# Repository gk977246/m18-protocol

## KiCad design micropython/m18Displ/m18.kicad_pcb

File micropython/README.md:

# M18 Protocol Micropython

Since someone posted pictures of Esp32-devices with display - I wanted such a device as quicktester.

I have no experience with micropython, but with help from qwen, i made a version for micropython.

Important: set Tx_pin low on boot(dumb charge count increases). I have added a boot.py file

## Hardware

I made a test pcb with Esp32C3-mini, Oled or Spi-display, and uart connections for cyd

Includes Mp1584 (buck-module), level-shifter, and Spud-Isolator

## Dont use Cyd with buck converter(the dumb charge counter increases) -- power it with usb and use read-button

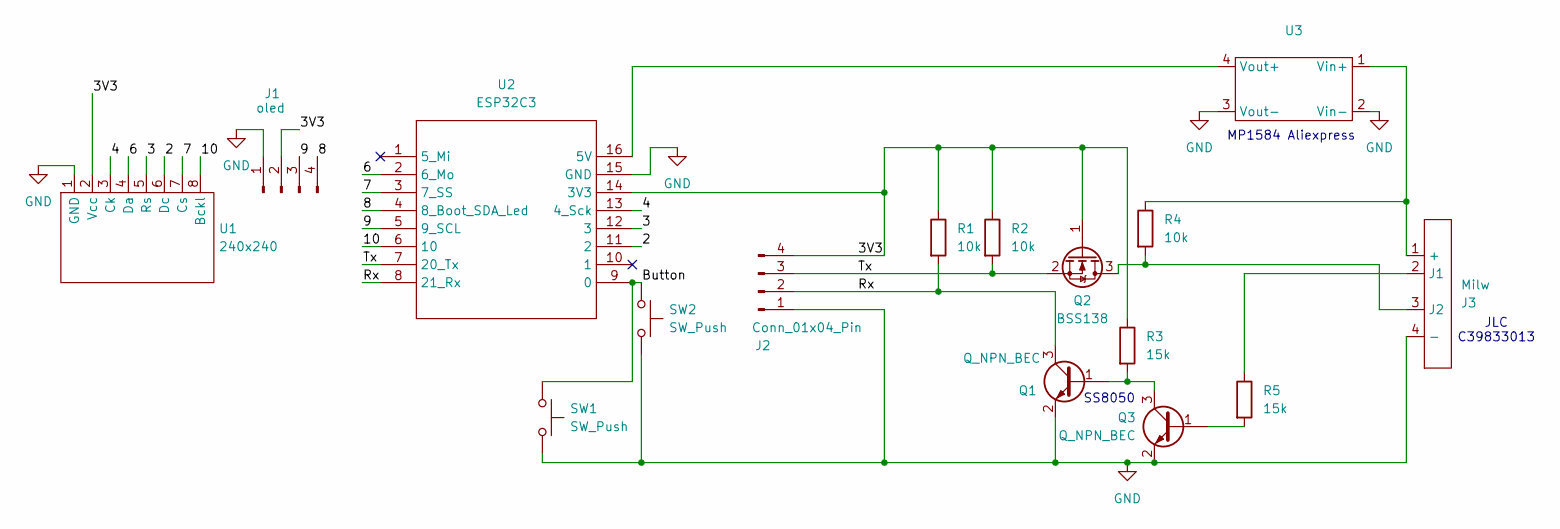
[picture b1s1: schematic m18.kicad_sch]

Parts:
J1: oled; 128x64Oled4Pin
J2: Conn_01x04_Pin; PinSocket_1x04_P2.54mm_Vertical
J3: Milw; Milw_Spade
Q1, Q3: Q_NPN_BEC; SOT-23
Q2: BSS138; SOT-23
R1, R2, R4: 10k; R_0603_1608Metric
R3, R5: 15k; R_0603_1608Metric
SW1: SW_Push; Sw_edge
SW2: SW_Push; SW_Push_1P1T_NO_6x6mm_H9.5mm
U1: 240x240; 170x320_7789
U2: ESP32C3; Esp32_C3_mini_module
U3: mp1584

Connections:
/2: U1.6 (Dc), U2.11 (2)
/3: U1.5 (Rs), U2.12 (3)
/3V3: J1.2, J2.4, Q2.1 (G), R1.1, R2.1, R3.1, U1.2 (Vcc), U2.14 (3V3)
/4: U1.3 (Ck), U2.13 (4_Sck)
/6: U1.4 (Da), U2.2 (6_Mo)
/7: U1.7 (Cs), U2.3 (7_SS)
/8: J1.4, U2.4 (8_Boot_SDA_Led)
/9: J1.3, U2.5 (9_SCL)
/10: U1.8 (Bckl), U2.6 (10)
/Button: SW1.1, SW2.1, U2.9 (0)
/Rx: J2.2, Q1.3 (C), R1.2, U2.8 (21_Rx)
/Tx: J2.3, Q2.2 (S), R2.2, U2.7 (20_Tx)
GND: J1.1, J2.1, J3.4 (-), Q1.2 (E), Q3.2 (E), SW1.2, SW2.2, U1.1 (GND), U2.15 (GND), U3.2 (Vin-), U3.3 (Vout-)
unnamed: J3.1 (+), R4.1, U3.1 (Vin+)
unnamed: J3.2 (J1), R5.1
unnamed: J3.3 (J2), Q2.3 (D), R4.2
unnamed: Q1.1 (B), Q3.3 (C), R3.2
unnamed: Q3.1 (B), R5.2
unnamed: U2.16 (5V), U3.4 (Vout+)

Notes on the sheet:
SS8050
MP1584 Aliexpress
JLC C39833013

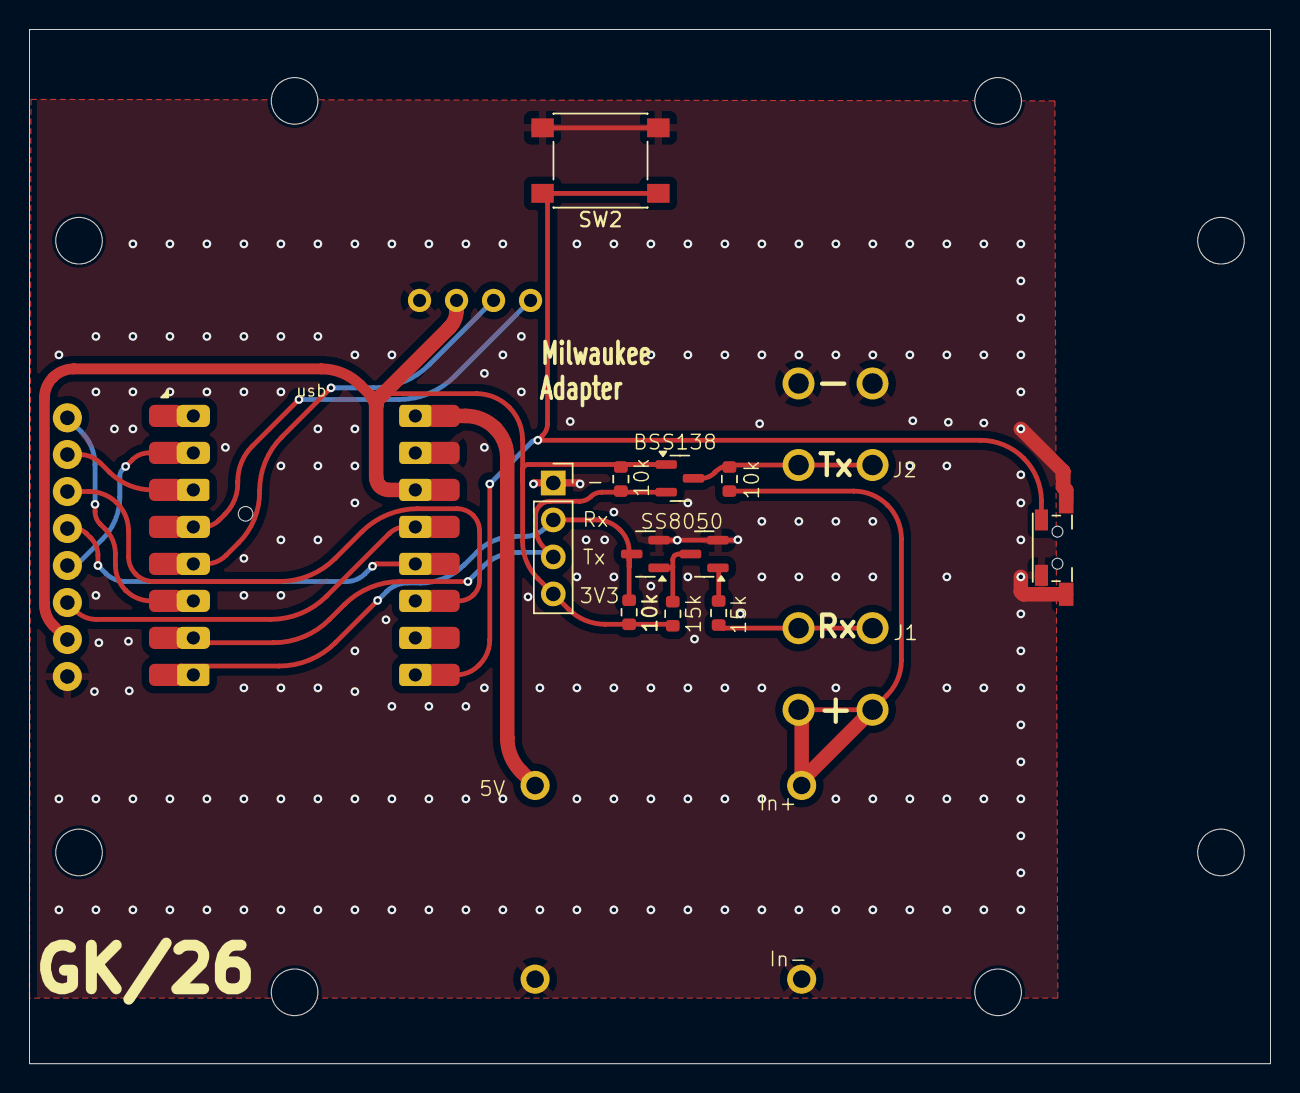
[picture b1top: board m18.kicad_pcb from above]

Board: 2 copper layers, 85.2 x 71.0 mm, 16 parts (0 on the bottom side), 19 nets.

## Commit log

2026-04-25 micropython folder
2026-04-27 boot pins
2026-05-02 Update milwaukee_main.py
    scale font
